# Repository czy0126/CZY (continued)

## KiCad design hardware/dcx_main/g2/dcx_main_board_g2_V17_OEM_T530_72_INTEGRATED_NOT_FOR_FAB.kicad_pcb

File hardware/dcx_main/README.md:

# DCX 主功率板 —— 原生原理图（A1）

> **最新状态：NOT_FOR_FAB / A1-WIP。** 本目录已移入当前开发分支，保留嘉立创原生 `.eprj2` 和真实焊盘比对。**`netlist_compare.json:readiness=PARTIAL_PASS` 不是完整原理图或投板验收。**
> 17 个 BOM 真实外围（R7–R10、C13、C101–C112）与**五只磁件（T1–T4、CT）**都已画进原生原理图并逐焊盘核对；
> 但外围仍是**值/MPN 占位件**，磁件的引脚号是**逻辑端子名**而不是厂商端子图，物理端子号/极性、
> GUI ERC 与带网 PCB 全部未完成。详见 [磁件符号逻辑合同](magnetics_symbol_contract.json)、[61 件真实选型登记表](component_decision_register.json)、[厂家 24 个端子回填表](vendor_terminal_request.json) 和 [外部阻塞解除与执行协议](../../docs/D1_外部阻塞解除与测试交付_2026-11-02.md)。

这是 `design/v3/pcb/board_netlist.csv`（由 v3 deck 派生的**金网表**）在嘉立创 EDA Pro 里的
原生可编辑原理图，不是一份新的设计。器件、网络、位号全部来自金网表；本目录只解决一件事：
把 SPICE 的 `G/S/D` 引脚名落到真实封装的**具体焊盘**上，并证明落对了。

项目文件：`dcx_main_board.eprj2`（嘉立创 EDA Pro 4.1.60，`.eprj2` 是 SQLite）。
打开方式：复制到嘉立创客户端的工程目录（本项目已改为 `D:\workshop\LCEDA-Pro\projects\`，
见 `%USERPROFILE%\Documents\LCEDA-Pro\config.json` 的 `APP_PROJECT_DIR`），在客户端里打开即可编辑。
**本仓库只有原理图，没有 PCB**——headless 下 PCB 相关 API 不可用，见下。

## 已验证的结论

| 结论 | 证据 |
|------|------|
| **83 个位号**已放置：金网表 66 只 + BOM 真实外围 17 只，**285 个焊盘**全部有归属（280 个接线、5 个按设计留空） | `pin_footprint_review.csv` |
| 按 A1 任务卡的**六个功能块**绘制，每块有标题文字，块内按功能排列 | `gen/slice_00.js` 的 `labels` |
| 金网表的 193 个引脚展开成 **245 个焊盘**，逐焊盘比对**无一错接、无一漏接** | `netlist_compare.json:pads_checked` |
| 17 个外围的 **34 个焊盘**按 `pin_connections.csv` 连接并单独计数，不混进金网表的 245 | `peripheral_pads_checked` |
| U2（UCC27282）裸露焊盘按设计接 PGND，单独计数，**不算进**金网表的 245 | `pads_bonded_by_design` |
| T1–T4、CT **已放置并逐焊盘核对**，引脚号是逻辑端子名（`PRI_A`/`SEC_A`/`CTAP`），**不是**厂商端子号 | `magnetics_symbol_contract.json` |
| 五只磁件的**物理端子号与 DOT 仍未核实**，所有 `physical_pad` 保持 null | `physical_pad_map_verified: false` |
| 83 个位号里 **61 个仍是占位件**（39 原有 + 22 新增外围/磁件；值未定或封装不对），审表里逐行标注 `PLACEHOLDER` | `pin_footprint_review.csv` 的 `note` 列 |

比对是按**焊盘**做的，不是按位号数量做的。这一步是必要的：金网表把 MOS 的引脚叫 `S`，
而 DFN/TDSON 封装的源极是 1、2、3 三个焊盘——只连其中一个，导出的网表仍然"和金网表一致"，
错误要到出铜箔才暴露。

## 评审用的导出图

**`main_board.svg` 目前是过期的**（仍停在磁件放上去之前的 78 个位号）。加进五只磁件后
`getSvgFile` 在 60 s 的 invoke 上限内返回不了：实测两次都在 59750 ms 超时
（`REQUEST_TIMEOUT`），而 CLI 的单次上限写死在 60000 ms。要么在 GUI 里导出，
要么等 A1 收尾时再试。**不要把旧 SVG 当作当前图的证据。**

导出的用法（`gen/export_svg.js` 调 `sch_ManufactureData.getSvgFile`）：

```bash
/d/lceda-pro/lceda-pro.exe invoke --session <id> --ext-uuid eda --timeout 60000 \
    --code "$(cat hardware/dcx_main/gen/export_svg.js)" > /tmp/svg.json
python -c "import json;open('hardware/dcx_main/main_board.svg','w',encoding='utf-8') \
    .write(json.load(open('/tmp/svg.json',encoding='utf-8'))['value']['svg'])"
```

`getSvgFile` 返回整个文件，CLI 输出很大，所以必须重定向；`getPngFile` 也在，但 SVG 可读、可比对。

## 图纸怎么分区

A1 任务卡要求按六部分绘图，`tools/main_board_schematic.py` 的 `SECTIONS` 就是这六块，
放置顺序按信号链：输入/半桥 → 谐振腔与 T1–T4 → 四组 SR → 控制（UCC25600/UCC27282）
→ 偏置/OC/启动 → 输出接口。每块画一个标题文字。

`test_every_placed_ref_sits_in_exactly_one_section` 要求**每个位号恰好落在一块里**：
少一块会被发现（否则器件留在原地），多一块也会被发现（否则被放两次）。
测试还把 `SECTIONS` 的全部位号与金网表的 66 个位号做了集合相等——新增/删除位号不会静默掉队。

审表的 `review_status` 只有四种取值：`MAPPED`、`BONDED BY DESIGN`、`OPEN - REASON GIVEN`、
`OPEN - NEEDS DECISION`。最后一个必须是空的——留一格空白和"已审过"看起来一模一样，
所以测试 `test_every_review_row_carries_a_status_and_a_basis` 直接把它当失败条件。

## 引脚映射从哪来

`library_pins.json` 是对运行中的嘉立创 EDA 客户端**实测**导出的（`gen/probe_all_pins.js`，
按精确 MPN 搜索解析器件，不依赖记忆里的 uuid）。模块里没有任何猜出来的引脚号：

- 器件引脚号覆盖不到金网表的引脚名 → `MappingError` 直接抛错，不静默跳过；
- 一个焊盘被两个不同网络认领 → 同样抛错（这是短路）。

`tools/test_main_board_schematic.py` 会**重新**从 `library_pins.json` 推导 MOS 的 G/S/D 焊盘组，
再和代码里的常量比对——库版本更新导致焊盘重新编号时，红的应该是这个测试。

## 与金网表的唯一一处偏离

`U2` 的焊盘 11 是 VSON-10 的**裸露焊盘**，SPICE 模型里没有它，金网表无从表达。
它在实际器件上是散热路径，也是门驱动开关所参考的电位，悬空是错的，因此接 `PGND`。
这一行在审表里写作 `BONDED BY DESIGN`，在 `netlist_compare.json` 里进
`pads_bonded_by_design` 而不是进 `pads_checked`——**不把它混进金网表的数字里**。

`D_CT1..4` 焊盘 2（BAT54 的第二只阳极）和 `U2` 焊盘 2（datasheet 标 NC）留空，
审表里写明了理由；工具会把"留空"和"漏画"分别报告。

## 金网表之外：17 个真实外围

金网表由 SPICE deck 派生，**表达不了** EN/RUN 默认电平、手动 RUN 跳线、EN 滤波和每只控制 IC 的
VDD 去耦。它们由 `main_board_schematic.py:PERIPHERALS` 单独声明，**不塞进金网表**——
否则"deck 完整"就会被误读成"板子完整"，而制造门槛也就失去了区分能力。

| 位号 | 连接 | BOM 冻结值 |
|---|---|---|
| R7 | RUN–PGND | 10 kΩ |
| R8 | VCC12–RUN（手动 RUN 跳线） | 1 kΩ |
| R9 | GD1–PGND（U2 HI 默认关断） | 10 kΩ |
| R10 | GD2–PGND（U2 LI 默认关断） | 10 kΩ |
| C13 | RUN–PGND（U2 EN 滤波） | 1 nF |
| C101/C102 … C111/C112 | 每只 IC 的 VDD–PGND | 1 µF + 100 nF |

网络名取自 `design/v1/pin_connections.csv` 的**引脚位置**：U2.6=EN 在金网表里叫 `RUN`，
U2.7/8=HI/LI 叫 `GD1`/`GD2`；`12V_P` 在金网表里叫 `VCC12`。测试
`test_every_peripheral_net_is_a_net_the_golden_netlist_already_uses` 锁住这一点，
防止把 CSV 的名字直接搬进原理图、造出一个没人共享的网络（那种错误在图上看起来完全正常）。

它们**不是**新设计：BOM 已有这些行、值已冻结；缺的是 MPN/封装与布局。所以审表仍标
`PLACEHOLDER`，制造门槛也仍不会因为"17 只都画了"而变绿。

## ERC：本站这一轮**不能**用 CLI 签核

`eda.sch_Drc.check()` 是这次客户端里唯一可用的电气规则入口（`Object.getOwnPropertyNames`
显示 `sch_Drc` 原型上只有 `constructor` 和 `check`，没有 `getCheckErrorList` 之类能取明细的接口）。
它 `verbose=false` 返回布尔、`verbose=true` 返回 `[{type, count}]` 直方图，**两个都不给明细**。

实测这个直方图**不随图页内容变化**，所以它的数字不能当 ERC 结论引用：

| 页面状态 | `check(true,false,true)` |
|----------|--------------------------|
| 61 个器件、222 根线 | `warn ×5` |
| 额外放一只**完全未连线的**电阻 | `warn ×5`（不变） |
| 删掉该电阻 | `warn ×5`（不变） |
| **清空整页**（0 个器件） | **`warn ×8`**（反而更多） |

清空后反而变多，说明这个计数不是"这张图页的 ERC 结果"。复现脚本：
`gen/drc_ab.js`、`gen/drc_empty_test.js`（后者会清空图页，跑完必须用
`python tools/lceda_place_main_board.py --all` 恢复）。

**所以 ERC 必须在 GUI 里手工跑一次并截图存档**，本目录不提供 ERC 通过的证据。
这一点写在这里，是为了防止后来者把"5 个 warning"当成一个已知的、已被解释掉的数字。

## 重新生成

```bash
python tools/main_board_schematic.py --write      # -> placement_plan.json + pin_footprint_review.csv
python tools/lceda_place_main_board.py --emit     # -> gen/slice_NN.js
# 必须按路径打开，且在本会话里不要再调 dmt_Project.openProject(uuid)
/d/lceda-pro/lceda-pro.exe open --path "$(pwd -W)/hardware/dcx_main/dcx_main_board.eprj2" --headless true
python tools/lceda_place_main_board.py --all --session <id> --watch hardware/dcx_main/dcx_main_board.eprj2
python tools/lceda_place_main_board.py --netlist-ready --session <id>   # 仅内存，见下
/d/lceda-pro/lceda-pro.exe invoke --session <id> --ext-uuid eda --timeout 60000 \
    --code "$(cat hardware/dcx_main/gen/export_netlist.js)" > hardware/dcx_main/gen/netlist_export_raw.json
python tools/check_main_board_netlist.py          # A4 验收：ok 必须为 True
```

`--session` 是客户端 CLI 会话 id；一次 invoke 上限 **60000 ms**（`--help` 里写的 1800000 是错的）。
放置分 4 片跑，`slice_00.js` 会先清空图页，所以**重跑 `--all` 就是完整的重建**。

三条 headless 实测规律，违反任何一条都会得到"看起来成功、其实没写盘"的结果：

1. **只能用 `--path` 打开工程**。在脚本里调 `dmt_Project.openProject(uuid)` 会让编辑器重新解析到
   云端/库里的副本，此后每次 `sch_Document.save()` 都返回 false、文件 mtime 不变。
   `getCurrentProjectInfo().uuid` 才是工程 uuid，`data[0]` 是名为 `Board1` 的板子而不是工程。
2. **`save()` 是防抖的**：返回 true 之后约 20 s 文件才变大。`--watch` 就是等这个变化；
   只看到 true 不能当作已写盘。
3. **保存与导出互斥**。项目库里的磁件器件带不上封装，而 `getNetlistFile()` 在磁件没有封装时
   什么都不返回；可一旦把 `otherProperty.Footprint` 注入已放置的实例，该文档就**无法再序列化**
   （save 恒 false），而且 `modify()` 会把这个字段搬进实例的 `footprint.uuid`。
   所以顺序固定：**先写盘，再用 `--netlist-ready` 在内存里注入封装 uuid，然后导出**；
   注入之后不能再 save，也不会写进 `.eprj2`。仓库里保存的原生工程因此没有磁件封装关联，
   网表证据来自那一步内存注入。

## 已知缺口（本目录没有假装它们不存在）

1. **磁件的物理端子仍未核实**（原来的"没有符号"已解决）：`DCX_XFMR_5P` / `DCX_CT_4P`
   两个原生符号已建、已放置，引脚号是逻辑端子名。缺的是绕组厂的端子图，把
   `PRI_A`/`SEC_A`/`CTAP` 变成带 DOT 的编号焊盘。在那之前 `physical_pad` 全部是 null，
   `physical_pad_map_verified` 全部是 false——**名字对不等于极性对**。
2. **磁件的封装是占位件**：CT 的符号有 4 个端子，占位封装 `XFMR-TH_ZHT104A` 只有 2 个焊盘；
   变压器用 `XFMR-TH_5P-L20.5-W18.0-P3.25-TL`（5 焊盘）只是为了焊盘数对得上。
   它们让网表能导出、能比对，但不代表能投板。
3. **占位件**：Lr、Cr、Cin、Cout、D_BT 以及全部 R/C 的值仍是 `TO ASSIGN`，
   审表逐行标 `PLACEHOLDER`；它们连的是**对**的网络，但**不是**设计选定的料。
4. **没有 PCB**：`pcb_Document.importChanges` 返回 true 但导入 0 个器件，
   `dmt_Pcb.createPcb` 返回 undefined，`pcb_PrimitiveComponent.create` 抛 `[object Object]`。
   导入 PCB 需要在 GUI 里手工完成。
5. **没有网络表同步回路**：本目录的网表比对证明"原理图 = 金网表"，不证明
   "PCB = 原理图"。后者要靠 GUI 的导入和 DRC。

## 目录

```
dcx_main_board.eprj2          原生工程（可编辑，83 个位号）
library_pins.json             实测的器件引脚（11 类，来源 gen/pins_probe.json）
project_symbols.json          项目库里自建磁件符号的实测 uuid（由 gen/make_project_symbols.js 写入）
magnetics_symbol_contract.json 五只磁件的逻辑端子合同（由 tools/magnetics_cad_contract.py 生成）
placement_plan.json           每个位号 -> 器件 uuid + 焊盘->网络
pin_footprint_review.csv      A3 审表：285 行，含未接线焊盘的理由
netlist_compare.json          A4 比对结果
gen/probe_all_pins.js         按 MPN 实测引脚
gen/make_project_symbols.js   建两个磁件符号并回填 project_symbols.json
gen/export_netlist.js         导出客户端自己的网表
gen/slice_NN.js               放置脚本（由 --emit 生成）
gen/drc_ab.js                 证明 CLI ERC 直方图不随页面变化的实验
gen/drc_empty_test.js         清空页面再测 ERC（破坏性，跑完要 --all 恢复）
gen/api_probe.js              证明 eda.* 不是"什么都返回函数"的桩
gen/export_svg.js             导出评审用 SVG
main_board.svg                上述导出结果（2048×5273）——**已过期**，见上文
```

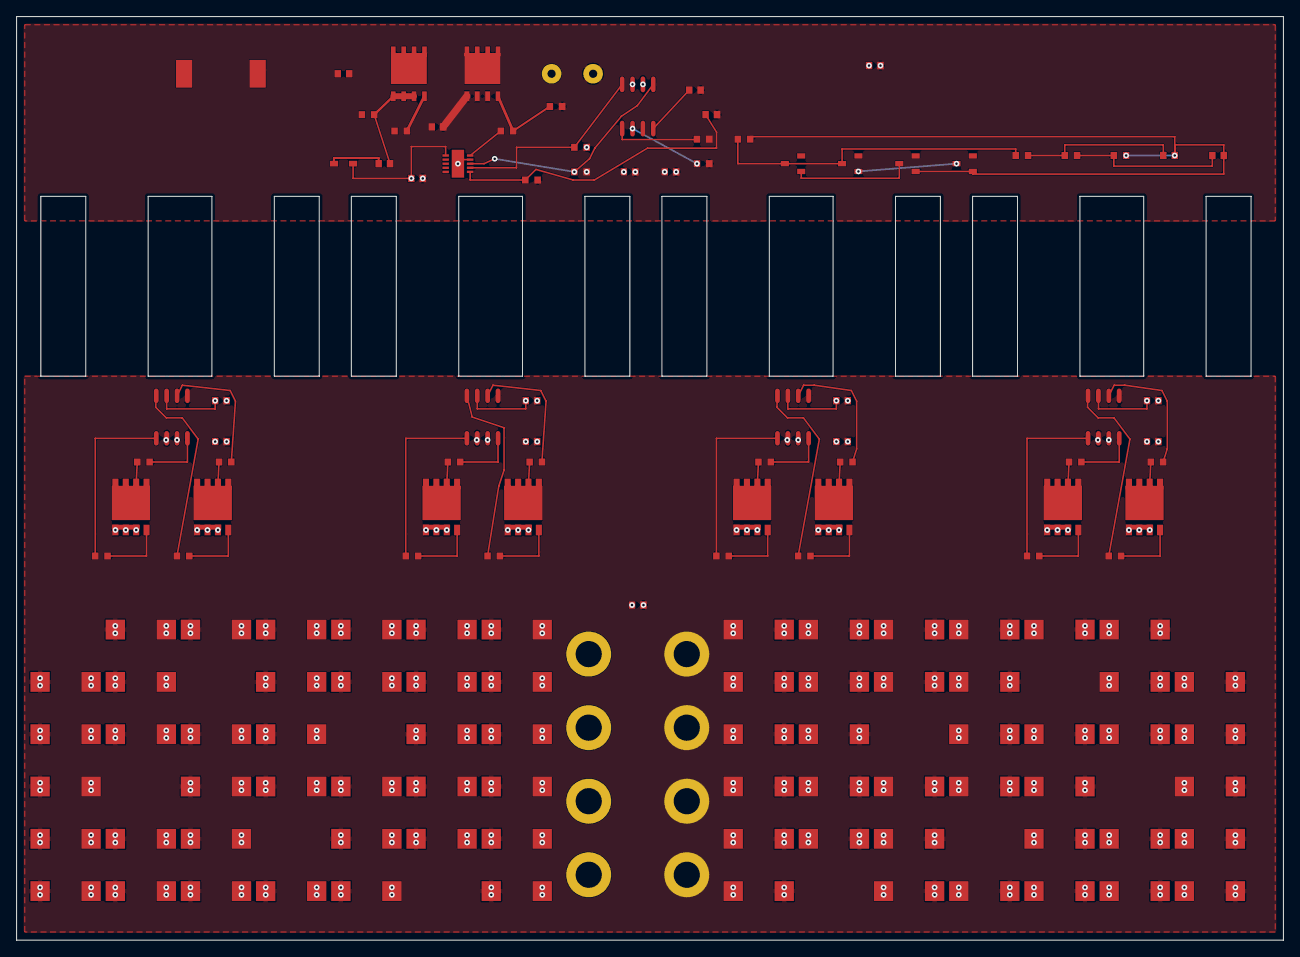
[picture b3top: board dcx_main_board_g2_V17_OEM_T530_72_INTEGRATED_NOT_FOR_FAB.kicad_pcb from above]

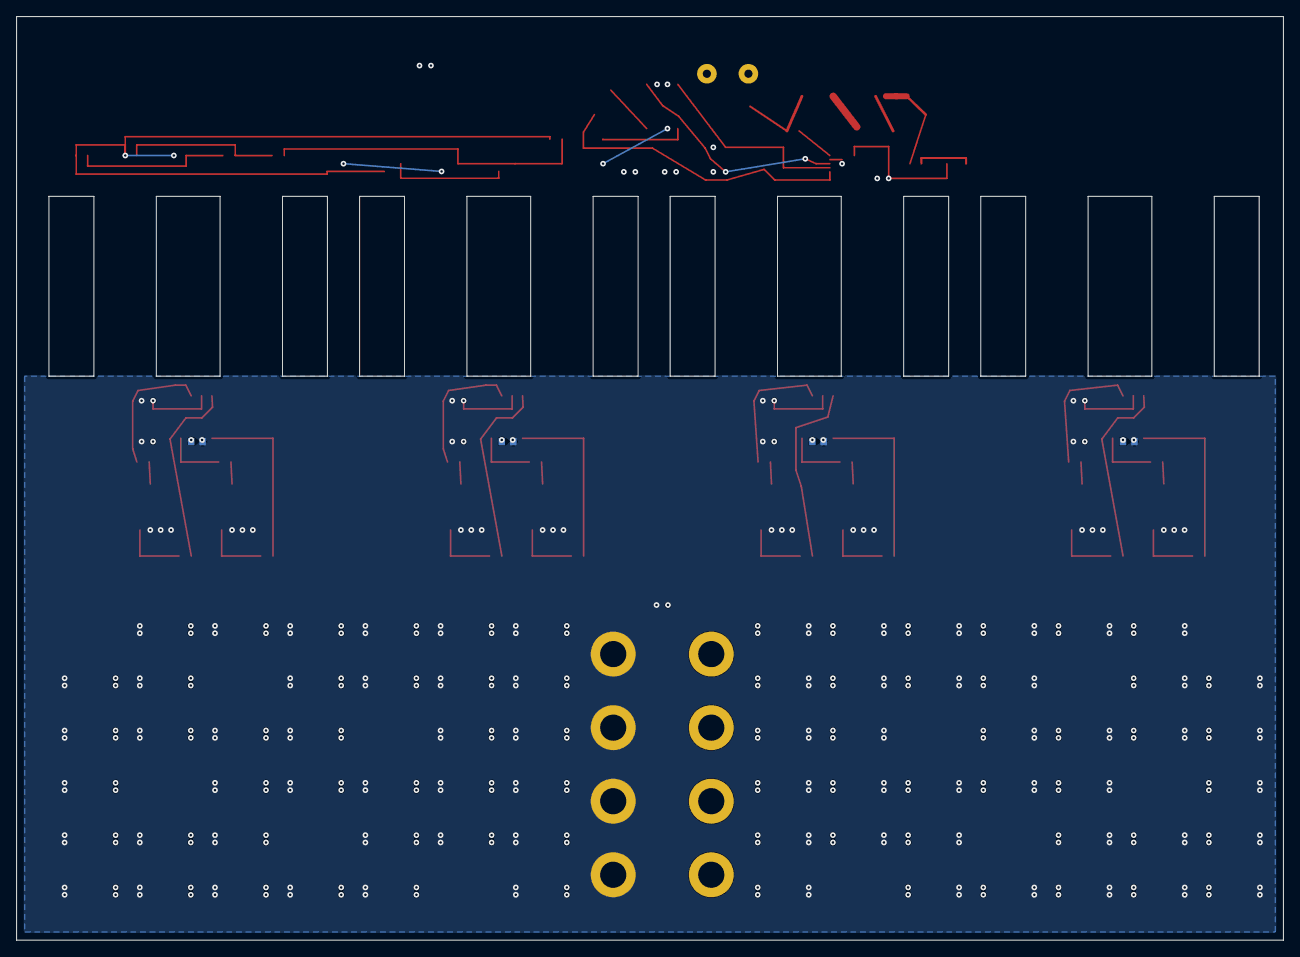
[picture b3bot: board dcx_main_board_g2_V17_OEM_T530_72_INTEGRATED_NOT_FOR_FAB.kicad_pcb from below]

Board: 12 copper layers, 155.0 x 113.0 mm, 149 parts (4 on the bottom side), 59 nets.

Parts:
C5, C6, C7, C8, C9, C10, C11, C12, C13, C101, C102, C103, C104, C105, C106, C107, C108, C109, C110, C111, C112: V15_PROVISIONAL_CAD_ONLY
CHB01, CHB02, CHB03, CHB04, CHB05, CHB06, CHB07, CHB08, CHB09, CHB10, CHB11, CHB12, CHB13, CHB14, CHB15, CHB16, CHB17, CHB18, CHB19, CHB20, CHB21, CHB22, CHB23, CHB24, CHB25, CHB26, CHB27, CHB28, CHB29, CHB30, CHB31, CHB32, CHB33, CHB34, CHB35, CHB36, CHB37, CHB38, CHB39, CHB40, CHB41, CHB42, CHB43, CHB44, CHB45, CHB46, CHB47, CHB48, CHB49, CHB50, CHB51, CHB52, CHB53, CHB54, CHB55, CHB56, CHB57, CHB58, CHB59, CHB60, CHB61, CHB62, CHB63, CHB64, CHB65, CHB66, CHB67, CHB68, CHB69, CHB70, CHB71, CHB72: T530X477M006ATE004; KEMET_T530X_7343_43_OEM_B
Cin: V15_PROVISIONAL_CAD_ONLY
Cout: V15_PROVISIONAL_CAD_ONLY
Cr: V15_PROVISIONAL_CAD_ONLY
D_BT: V15_PROVISIONAL_CAD_ONLY
D_CT1, D_CT2, D_CT3, D_CT4: V15_PROVISIONAL_CAD_ONLY
J_IN: V15_PROVISIONAL_CAD_ONLY
J_OUT: EIGHT_PLATED_CONTACTS_VENDOR_UNRATED_NOT_FOR_FAB
Lr: V15_PROVISIONAL_CAD_ONLY
QH: V15_PROVISIONAL_CAD_ONLY
QL: V15_PROVISIONAL_CAD_ONLY
R1, R2, R3, R4, R5, R7, R9, R10, R15, R16, R17, R18, R19, R20, R21, R22, R23, R24, R25, R26, R27, R28, R29, R30, R31, R32, R33, R34, R35: V15_PROVISIONAL_CAD_ONLY
SR1A, SR1B, SR2A, SR2B, SR3A, SR3B, SR4A, SR4B: V15_PROVISIONAL_CAD_ONLY
U1, U2, U3, U4, U5, U6: V15_PROVISIONAL_CAD_ONLY

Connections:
CS1: D_CT1.1, D_CT3.3
CS2: D_CT2.1, D_CT4.3
DT: R1.1, U1.1
GA1: R20.2, SR1A.4
GA2: R22.2, SR2A.4
GA3: R24.2, SR3A.4
GA4: R26.2, SR4A.4
GB1: R21.2, SR1B.4
GB2: R23.2, SR2B.4
GB3: R25.2, SR3B.4
GB4: R27.2, SR4B.4
GD1: R9.1, U1.8, U2.7
GD2: R10.1, U1.5, U2.8
GH: QH.4, R4.2, R18.1
GH_DRV: R4.1, U2.4
GL: QL.4, R5.2, R19.1
GL_DRV: R5.1, U2.10
HB: C5.1, D_BT.1, U2.3
OC: C12.1, R16.2, R17.1, U1.3
OC1: C11.1, R15.2, R16.1
OCD: D_CT1.3, D_CT2.3, R3.1, R15.1
OCM: C11.2, C12.2, D_CT3.1, D_CT4.1, R3.2, R17.2
PGND: C6.2, C7.2, C8.2, C9.2, C10.2, C13.2, C101.2, C102.2, C103.2, C104.2, C105.2, C106.2, C107.2, C108.2, C109.2, C110.2, C111.2, C112.2, CHB01.2, CHB02.2, CHB03.2, CHB04.2, CHB05.2, CHB06.2, CHB07.2, CHB08.2, CHB09.2, CHB10.2, CHB11.2, CHB12.2, CHB13.2, CHB14.2, CHB15.2, CHB16.2, CHB17.2, CHB18.2, CHB19.2, CHB20.2, CHB21.2, CHB22.2, CHB23.2, CHB24.2, CHB25.2, CHB26.2, CHB27.2, CHB28.2, CHB29.2, CHB30.2, CHB31.2, CHB32.2, CHB33.2, CHB34.2, CHB35.2, CHB36.2, CHB37.2, CHB38.2, CHB39.2, CHB40.2, CHB41.2, CHB42.2, CHB43.2, CHB44.2, CHB45.2, CHB46.2, CHB47.2, CHB48.2, CHB49.2, CHB50.2, CHB51.2, CHB52.2, CHB53.2, CHB54.2, CHB55.2, CHB56.2, CHB57.2, CHB58.2, CHB59.2, CHB60.2, CHB61.2, CHB62.2, CHB63.2, CHB64.2, CHB65.2, CHB66.2, CHB67.2, CHB68.2, CHB69.2, CHB70.2, CHB71.2, CHB72.2, Cin.2, Cout.2, J_IN.2, J_OUT.2, QL.1, QL.2, QL.3, R1.2, R2.2, R7.2, R9.2, R10.2, R19.2, SR1A.1, SR1A.2, SR1A.3, SR1B.1, SR1B.2, SR1B.3, SR2A.1, SR2A.2, SR2A.3, SR2B.1, SR2B.2, SR2B.3, SR3A.1, SR3A.2, SR3A.3, SR3B.1, SR3B.2, SR3B.3, SR4A.1, SR4A.2, SR4A.3, SR4B.1, SR4B.2, SR4B.3, U1.6, U2.9, U2.11, U3.2, U3.5, U4.2, U4.5, U5.2, U5.5, U6.2, U6.5
REG1: C7.1, U3.3
REG2: C8.1, U4.3
REG3: C9.1, U5.3
REG4: C10.1, U6.3
RT: R2.1, U1.2
RUN: C13.1, R7.1, U2.6
SEC1_A: R28.1, SR1A.5, SR1A.6, SR1A.7, SR1A.8
SEC1_B: R29.1, SR1B.5, SR1B.6, SR1B.7, SR1B.8
SEC2_A: R30.1, SR2A.5, SR2A.6, SR2A.7, SR2A.8
SEC2_B: R31.1, SR2B.5, SR2B.6, SR2B.7, SR2B.8
SEC3_A: R32.1, SR3A.5, SR3A.6, SR3A.7, SR3A.8
SEC3_B: R33.1, SR3B.5, SR3B.6, SR3B.7, SR3B.8
SEC4_A: R34.1, SR4A.5, SR4A.6, SR4A.7, SR4A.8
SEC4_B: R35.1, SR4B.5, SR4B.6, SR4B.7, SR4B.8
SS: C6.1, U1.4
SW: C5.2, Cr.1, QH.1, QH.2, QH.3, QL.5, QL.6, QL.7, QL.8, QL.9, R18.2, U2.5
VCC12: C101.1, C102.1, C103.1, C104.1, D_BT.2, U1.7, U2.1
VCC12_S: C105.1, C106.1, C107.1, C108.1, C109.1, C110.1, C111.1, C112.1, U3.7, U4.7, U5.7, U6.7
VD1_A: R28.2, U3.4
VD1_B: R29.2, U3.6
VD2_A: R30.2, U4.4
VD2_B: R31.2, U4.6
VD3_A: R32.2, U5.4
VD3_B: R33.2, U5.6
VD4_A: R34.2, U6.4
VD4_B: R35.2, U6.6
VG1_A: R20.1, U3.1
VG1_B: R21.1, U3.8
VG2_A: R22.1, U4.1
VG2_B: R23.1, U4.8
VG3_A: R24.1, U5.1
VG3_B: R25.1, U5.8
VG4_A: R26.1, U6.1
VG4_B: R27.1, U6.8
VIN_P: Cin.1, J_IN.1, QH.5, QH.6, QH.7, QH.8, QH.9
VOUT: CHB01.1, CHB02.1, CHB03.1, CHB04.1, CHB05.1, CHB06.1, CHB07.1, CHB08.1, CHB09.1, CHB10.1, CHB11.1, CHB12.1, CHB13.1, CHB14.1, CHB15.1, CHB16.1, CHB17.1, CHB18.1, CHB19.1, CHB20.1, CHB21.1, CHB22.1, CHB23.1, CHB24.1, CHB25.1, CHB26.1, CHB27.1, CHB28.1, CHB29.1, CHB30.1, CHB31.1, CHB32.1, CHB33.1, CHB34.1, CHB35.1, CHB36.1, CHB37.1, CHB38.1, CHB39.1, CHB40.1, CHB41.1, CHB42.1, CHB43.1, CHB44.1, CHB45.1, CHB46.1, CHB47.1, CHB48.1, CHB49.1, CHB50.1, CHB51.1, CHB52.1, CHB53.1, CHB54.1, CHB55.1, CHB56.1, CHB57.1, CHB58.1, CHB59.1, CHB60.1, CHB61.1, CHB62.1, CHB63.1, CHB64.1, CHB65.1, CHB66.1, CHB67.1, CHB68.1, CHB69.1, CHB70.1, CHB71.1, CHB72.1, Cout.1, J_OUT.1

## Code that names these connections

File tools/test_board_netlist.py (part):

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
def test_high_side_fets_are_wired_across_the_input(netlist):
    _, rows, _ = netlist
    assert pins_of(rows, "QH") == {"D": "VIN_P", "S": "SW", "G": "GH"}
    assert pins_of(rows, "QL") == {"D": "SW", "S": "PGND", "G": "GL"}


def test_the_cavity_is_cr_then_ct_then_lr(netlist):
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    for i in (1, 2, 3, 4):
        pins = pins_of(rows, f"T{i}")
        assert len(pins) == 5, pins
        assert pins["CTAP"] == "VOUT"
        assert pins["SEC_A"] == f"SEC{i}_A"
        assert pins["SEC_B"] == f"SEC{i}_B"


def test_synchronous_rectifiers_go_from_secondary_to_pgnd(netlist):
    _, rows, _ = netlist
    for i in (1, 2, 3, 4):
        assert pins_of(rows, f"SR{i}A") == {"D": f"SEC{i}_A", "G": f"GA{i}", "S": "PGND"}
        assert pins_of(rows, f"SR{i}B") == {"D": f"SEC{i}_B", "G": f"GB{i}", "S": "PGND"}


def test_u1_pin_numbers_match_the_verified_map(netlist):
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def test_the_sr_controllers_carry_their_own_reg_caps(netlist):
    _, rows, _ = netlist
    for i, n in enumerate((3, 4, 5, 6), start=1):
        assert pins_of(rows, f"U{n}")["3"] == f"REG{i}"
        assert net_refs(rows, f"REG{i}") == [f"C{n + 4}", f"U{n}"]


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    for i in (1, 2, 3, 4):
        transformer = report["transformers"][f"T{i}"]
        a, b = transformer["secondary_a"], transformer["secondary_b"]
        assert (a["dot_pin"], a["non_dot_pin"]) == ("CTAP", "SEC_A")
        assert (b["dot_pin"], b["non_dot_pin"]) == ("SEC_B", "CTAP")
        assert a["dot_node"] == b["non_dot_node"] == "out"
        assert a["non_dot_node"] == f"a{i}"
        assert b["dot_node"] == f"b{i}"
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
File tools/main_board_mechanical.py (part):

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SOIC8_W, SOIC8_D, SOIC8_H = 7.4, 5.4, 1.75
# The REG crowbar (doc 34, package C: "紧接着连接选定的实际硬件关断电路").  Not a
# new circuit: it is the shutdown `pcb/sr_fault_validation` selected, with one
# copy per controller.  UCC24624 has no enable pin -- only a REG undervoltage or
# standby pulls VG low -- so pulling REG through 4.7 ohm (12.1 us) is the chosen
# route, against 75.5 ms for cutting VDD.
#
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    # 34, package C: "紧接着连接选定的实际硬件关断电路").  Placing U3-U6 needs no
    # ECO: the golden netlist, the BOM row "U3-U6" and theme section 3 already
    # carry them; what was missing was a pad to land on.  With them placed, each
    # VD*/VG* becomes a two-pad net and REG1-REG4 appear as the pin the REG
    # crowbar will pull.
    for i, x0 in enumerate(SR_X0, start=1):
        out.append(Part(f"U{i + 2}", "UCC24624DR", SOIC8_W, SOIC8_D, SOIC8_H,
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                        "kicad-library", SOIC8_FP,
                        note=f"dual SR controller for group {i}: pin 1/8 drive VG{i}_A/B "
                             f"through R{20 + 2 * (i - 1)}/R{21 + 2 * (i - 1)}, pin 4/6 "
                             f"sit on the drain Kelvin links, pin 3 (REG{i}) is the "
                             f"node a crowbar pulls, pin 7 is VCC12_S.  MPN from "
                             f"bom_draft.csv U3-U6 (ucc24624.pdf); land is the "
                             f"vendored KiCad SOIC-8, not a vendor drawing"))
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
